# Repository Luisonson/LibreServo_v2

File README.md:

# 
An Open source controller to convert any servo motor to the best smart servo.

This project was born as a necessity of mine to build a biped robot with intelligent servos to be able to “feel the muscles” to walk more human like. In the past we had OpenServo, and I think this project inherits something from it, but OpenServo died many years ago and it didn't reach my expectations anyway (power, communications...), and the commercial alternatives are way too expensive (Dynamixel, Herkulex, Lynxmotion...).

My goal with LibreServo is to make any standard servo the “smartest” one in the market. The "gold standard" nowadays is Robotis-Dynamixel, LibreServo should be better than that, that’s my goal at least.

A few characteristics of LibreServo:

    Compatible with standard servo motors (No need to change the bottom cover of them!)
    Voltage: From 4.5V up to 18V (Recommended: 5-14V)
    Communications: RS-485 half-duplex. Max Speed 9Mbps. Daisy chained. CRC-16
    Amp: Up to 16A continuous (WSD3069DN56) (Version >2.3)
    Micro-Controller: STM32F301k8 (cortex-M4@72MHz)
    Position sensor: Magnetic encoder, 16 bits of resolution! 360 degrees (AEAT-8800). Using the servo motor potentiometer will be possible to lower the cost but will lost precision and some characteristics.
    For the encoder I have designed 3D parts to substitute the potentiometer and used the same hole/space than the original.
    LibreServo will generate their own curves (sine ramps, trapezoidal ramps, hermitian curves...)
    Current sensor: +-15A ACS711
Communication Protocol: <a href="https://www.libreservo.com/en/articulo/libreservo-commands-part-one">LibreServo Commands</a><BR>

More info in <a href="https://www.libreservo.com/en">LibreServo</a>.

<p align="center">
</p>

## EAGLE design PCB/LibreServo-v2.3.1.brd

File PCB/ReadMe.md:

Here are the files (.brd and .sch) of KiCad 7.6.0 from LibreServo.<BR>
  In the "old" folder are the previous versions of the schematics.<BR>
  In the "Gerbers" folder are the production files.
#

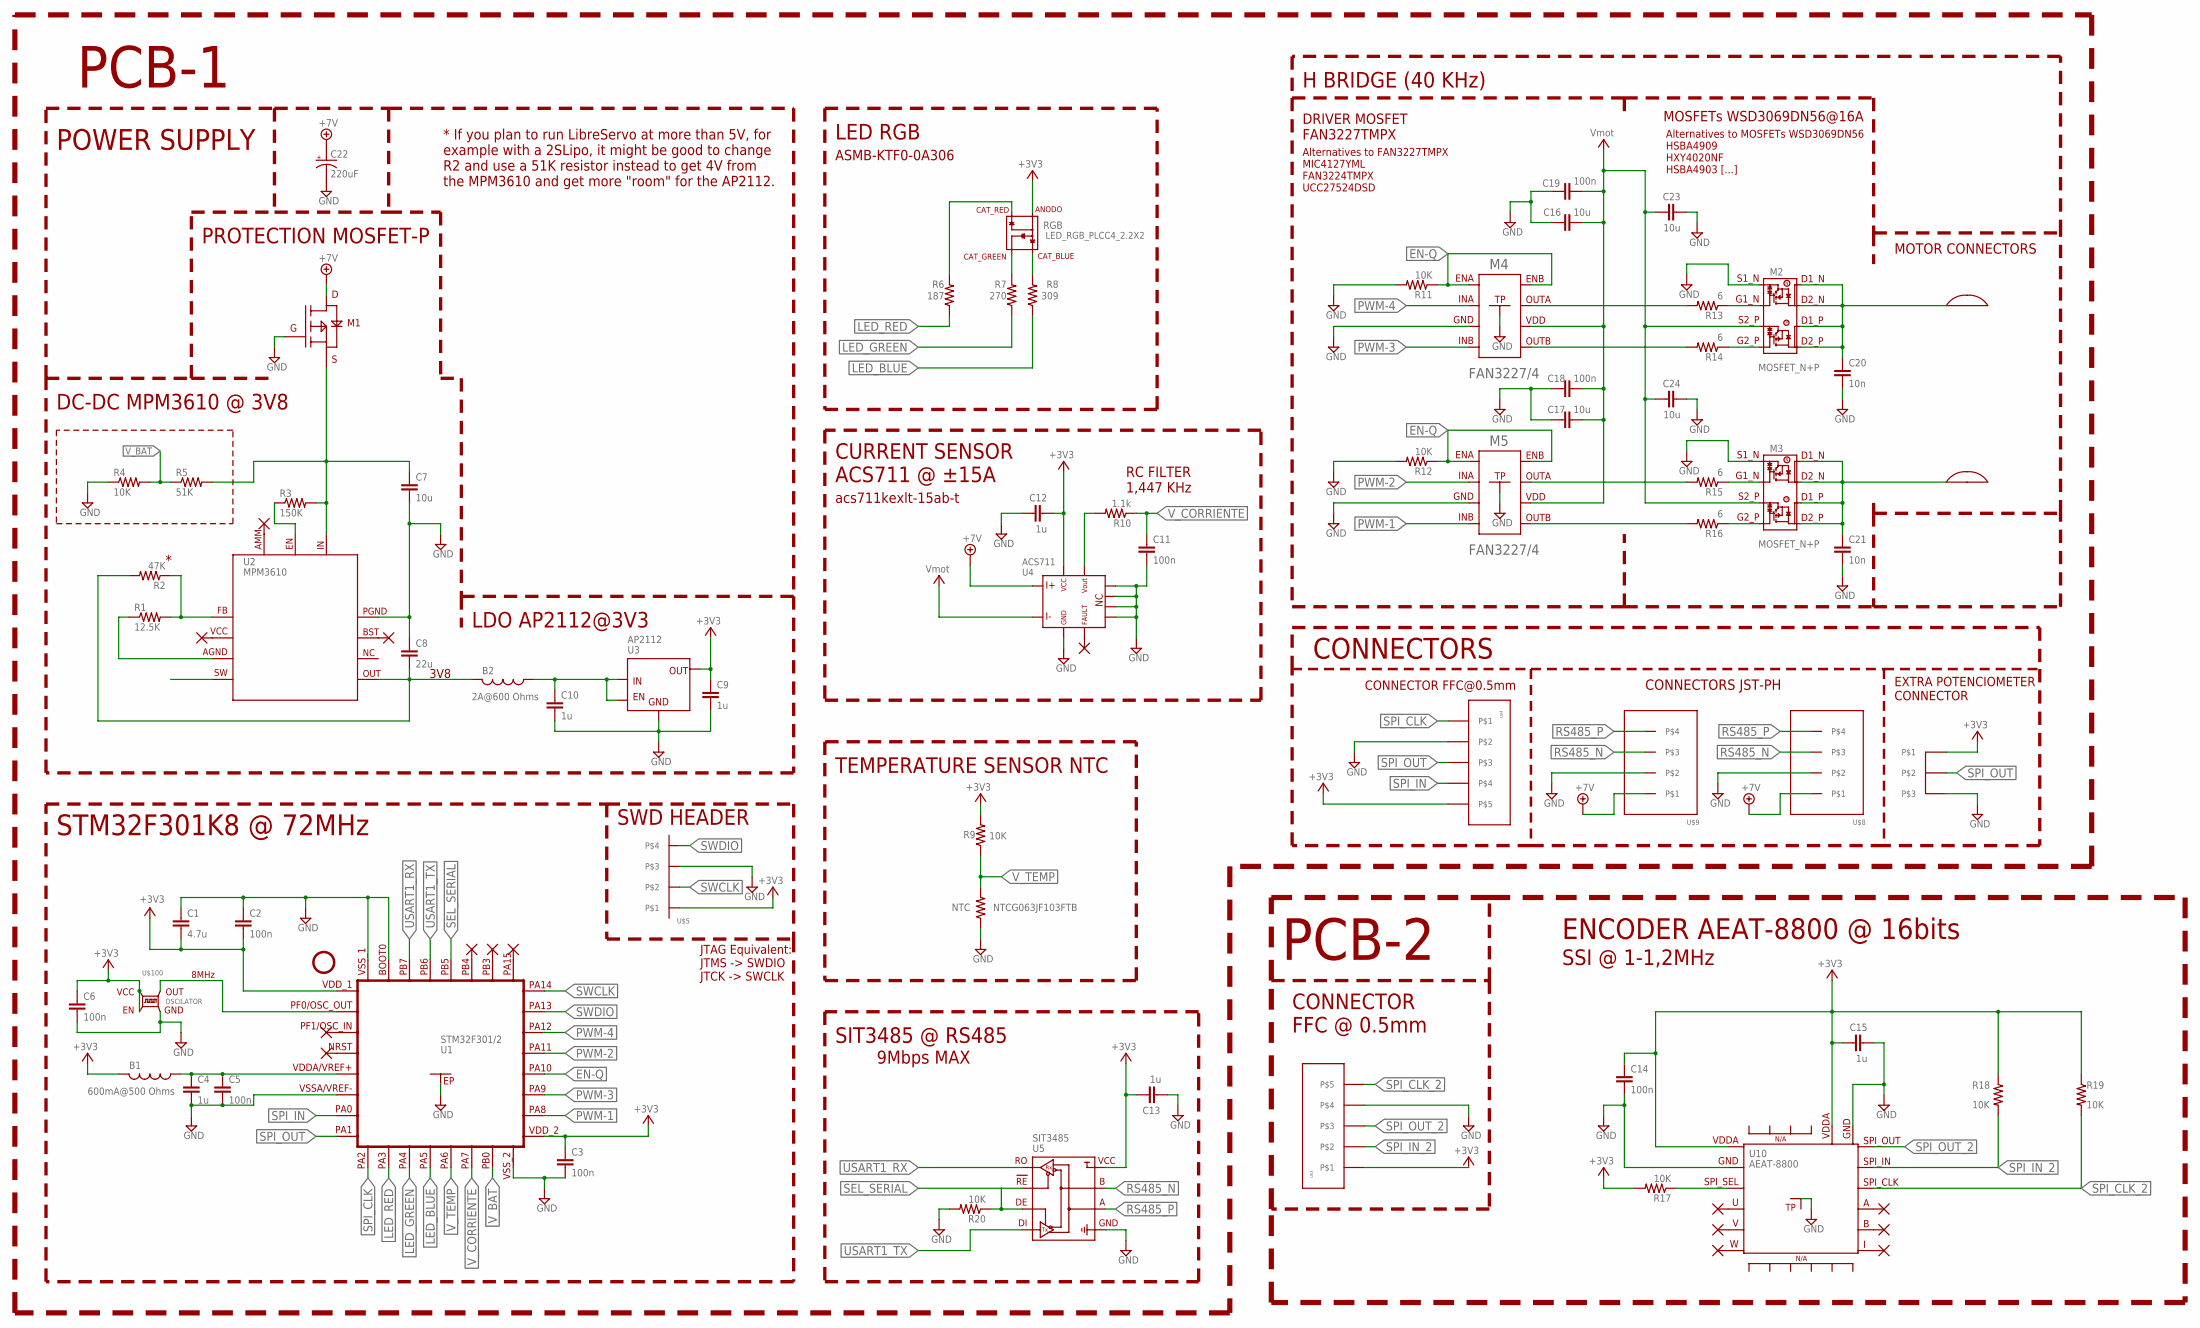
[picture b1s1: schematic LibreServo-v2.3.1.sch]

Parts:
B1: FERRITE_BEAD_0402; 0402
B2: FERRITE_BEAD_0603; 0603
C1: 4.7u; 0402
C2, C3, C5, C6, C11, C14, C18, C19: 100n; 0402
C4, C9, C10, C12, C13, C15: 1u; 0402
C7, C16, C17, C23, C24: 10u; 0603
C8: 22u; 1206
C20, C21: 10n; 0402
C22: 220uF; E2,5-6_MIN
M1: M1; SOT23
M2, M3: MOSFET_N+P; DFN5X6
M4, M5: FAN3227/4; MLP8
NTC: R-US0402_MIN; 0402_MIN
R1: 12.5K; 0402
R2: 47K; 0402
R3: 150K; 0402
R4, R9, R11, R12, R17, R18, R19, R20: 10K; 0402
R5: 51K; 0402
R6: 187; 0402
R7: 270; 0402
R8: 309; 0402
R10: 1.1k; 0402
R13, R14, R15, R16: 6; 0402
RGB: LED_RGB_PLCC4_2.2X2; PLCC-4_2.2X2
U1: STM32F301/2; QFN32
U2: MPM3610; MPM36XX
U3: AP2112; SOT25
U4: ACS711; ACS711-QFN
U5: SIT3485; MSOP-8
U10: AEAT-8800; QFN24
U$1, U$2: SLOT; SERVO_SLOT
U$3, U$4: FFC-5; FFC-5-0.5
U$5: HEADER_4_1.27_0.3
U$6: POTEN_SERVO
U$8, U$9: JST_PH-4_HOLEB; JST_PH-4_HOLE_B
U$100: OSCILATOR; OSC-2X1.6

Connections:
711_OUT: R10.2, U4.P$11
+3V3: B1.2, C1.2, C2.2, C3.1, C6.1, C9.1, C12.2, C13.2, R9.2, RGB.P$1 (ANODO), U1.1 (VDD_1), U1.17 (VDD_2), U3.5, U4.P$12, U5.P$8, U$4.P$5, U$5.P$1, U$6.P$1, U$100.P$1 (EN), U$100.P$4 (VCC)
+3V3_2: C14.1, C15.1, R17.2, R18.1, R19.1, U10.P$14, U10.P$19, U$3.P$1
+7V: C22.+, M1.P$2 (D), U4.P$1, U$8.P$1, U$9.P$1
CLK-8MHZ: U1.2 (PF0/OSC_IN), U$100.P$3 (OUT)
EN-Q: M4.P$1 (ENA), M4.P$8 (ENB), M5.P$1 (ENA), M5.P$8 (ENB), R11.1, R12.1, U1.20 (PA10)
GND: C1.1, C2.1, C3.2, C4.2, C5.2, C6.2, C7.2, C8.1, C9.2, C10.2, C11.2, C12.1, C13.1, C16.1, C17.1, C18.1, C19.1, C20.2, C21.2, C22.-, C23.2, C24.2, M1.P$1 (G), M2.P$1 (S1_N), M3.P$1 (S1_N), M4.P$3 (GND), M4.P$9 (TP), M5.P$3 (GND), M5.P$9 (TP), NTC.1, R4.1, R11.2, R12.2, R20.2, U1.6 (VSSA/VREF-), U1.16 (VSS_2), U1.31 (BOOT0), U1.32 (VSS_1), U1.EP, U2.P$12 (P$8_PGND), U2.P$13 (P$8_PGND), U2.P$14 (P$8_PGND), U3.2, U4.P$5, U4.P$7, U4.P$8, U4.P$9, U4.P$10, U5.P$5, U$4.P$2, U$5.P$3, U$6.P$3, U$8.P$2, U$9.P$2, U$100.P$2 (GND)
GND_2: C14.2, C15.2, U10.P$13, U10.P$20, U10.P$25, U$3.P$4
IN_AP2112: B2.1, C10.1, U3.1, U3.3
LED_BLUE: R8.1, U1.12 (PA5)
LED_GREEN: R7.1, U1.11 (PA4)
LED_RED: R6.1, U1.10 (PA3)
M1-OUT: C7.1, M1.P$3 (S), R3.2, R5.2, U2.P$16 (P$9_IN)
M2-OUT: C20.1, M2.P$5 (D2_P), M2.P$6 (D1_P), M2.P$7 (D2_N), M2.P$8 (D1_N), M2.P$9 (D1_N), U$1.P$1
M3-OUT: C21.1, M3.P$5 (D2_P), M3.P$6 (D1_P), M3.P$7 (D2_N), M3.P$8 (D1_N), M3.P$9 (D1_N), U$2.P$1
M4-OUTA: M4.P$7 (OUTA), R13.2
M4-OUTA-IN: M2.P$2 (G1_N), R13.1
M4-OUTB: M4.P$5 (OUTB), R14.2
M4-OUTB-IN: M2.P$4 (G2_P), R14.1
M5-OUTA: M5.P$7 (OUTA), R15.2
M5-OUTA-IN: M3.P$2 (G1_N), R15.1
M5-OUTB: M5.P$5 (OUTB), R16.2
M5-OUTB-IN: M3.P$4 (G2_P), R16.1
MPM3610_AGND: R1.1, U2.P$3 (P$3_AGND)
MPM3610_EN: R3.1, U2.P$17 (P$10_EN)
MPM3610_FB: R1.2, R2.1, U2.P$1 (P$1_FB)
MPM3610_SW: U2.P$4 (P$4_SW), U2.P$5 (P$4_SW), U2.P$6 (P$4_SW)
unnamed: R6.2, RGB.P$4 (CAT_RED)
unnamed: R7.2, RGB.P$3 (CAT_GREEN)
unnamed: R8.2, RGB.P$2 (CAT_BLUE)
unnamed: R17.1, U10.P$21
OUT_MPM3610: B2.2, C8.2, R2.2, U2.P$7 (P$5_OUT), U2.P$8 (P$5_OUT), U2.P$9 (P$5_OUT)
PWM-1: M5.P$4 (INB), U1.18 (PA8)
PWM-2: M5.P$2 (INA), U1.21 (PA11)
PWM-3: M4.P$4 (INB), U1.19 (PA9)
PWM-4: M4.P$2 (INA), U1.22 (PA12)
RS485_N: U5.P$7, U$8.P$3, U$9.P$3
RS485_P: U5.P$6, U$8.P$4, U$9.P$4
SEL_SERIAL: R20.1, U1.28 (PB5), U5.P$2, U5.P$3
SPI_CLK: U1.9 (PA2), U$4.P$1
SPI_CLK_2: R19.2, U10.P$10, U$3.P$5
SPI_IN: U1.7 (PA0), U$4.P$4
SPI_IN_2: R18.2, U10.P$11, U$3.P$2
SPI_OUT: U1.8 (PA1), U$4.P$3, U$6.P$2
SPI_OUT_2: U10.P$12, U$3.P$3
SWCLK: U1.24 (PA14), U$5.P$2
SWDIO: U1.23 (PA13), U$5.P$4
USART1_RX: U1.30 (PB7), U5.P$1
USART1_TX: U1.29 (PB6), U5.P$4
VDDA-FILTRADO: B1.1, C4.1, C5.1, U1.5 (VDDA/VREF+)
VMOT: C16.2, C17.2, C18.2, C19.2, C23.1, C24.1, M2.P$3 (S2_P), M3.P$3 (S2_P), M4.P$6 (VDD), M5.P$6 (VDD), U4.P$3
V_BAT: R4.2, R5.1, U1.15 (PB0)
V_CORRIENTE: C11.1, R10.1, U1.14 (PA7)
V_TEMP: NTC.2, R9.1, U1.13 (PA6)

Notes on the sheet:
SWD HEADER
STM32F301K8 @ 72MHz
POWER SUPPLY
PROTECTION MOSFET-P
DC-DC MPM3610 @ 3V8
LDO AP2112@3V3
LED RGB
ASMB-KTF0-0A306
CURRENT SENSOR ACS711 @ ±15A
RC FILTER 1,447 KHz
TEMPERATURE SENSOR NTC
SIT3485 @ RS485
H BRIDGE (40 KHz)
DRIVER MOSFET FAN3227TMPX
MOSFETs WSD3069DN56@16A
MOTOR CONNECTORS
PCB-2
ENCODER AEAT-8800 @ 16bits
CONNECTOR FFC @ 0.5mm
CONNECTORS
CONNECTOR FFC@0.5mm
CONNECTORS JST-PH
EXTRA POTENCIOMETER CONNECTOR
PCB-1
acs711kexlt-15ab-t
3V8
2A@600 Ohms
600mA@500 Ohms
NTCG063JF103FTB
SSI @ 1-1,2MHz
9Mbps MAX
8MHz
* If you plan to run LibreServo at more than 5V, for example with a 2SLipo, it might be good to change R2 and use a 51K resistor instead to get 4V from the MPM3610 and get more "room" for the AP2112.
Alternatives to FAN3227TMPX MIC4127YML FAN3224TMPX UCC27524DSD
Alternatives to MOSFETs WSD3069DN56 HSBA4909 HXY4020NF HSBA4903 [...]
JTAG Equivalent: JTMS -> SWDIO JTCK -> SWCLK

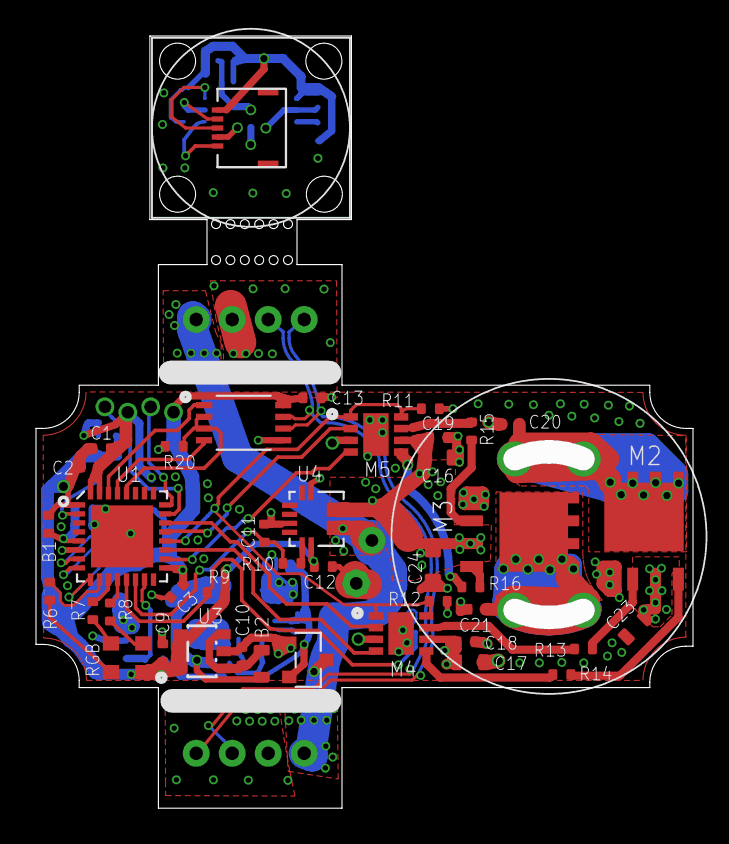
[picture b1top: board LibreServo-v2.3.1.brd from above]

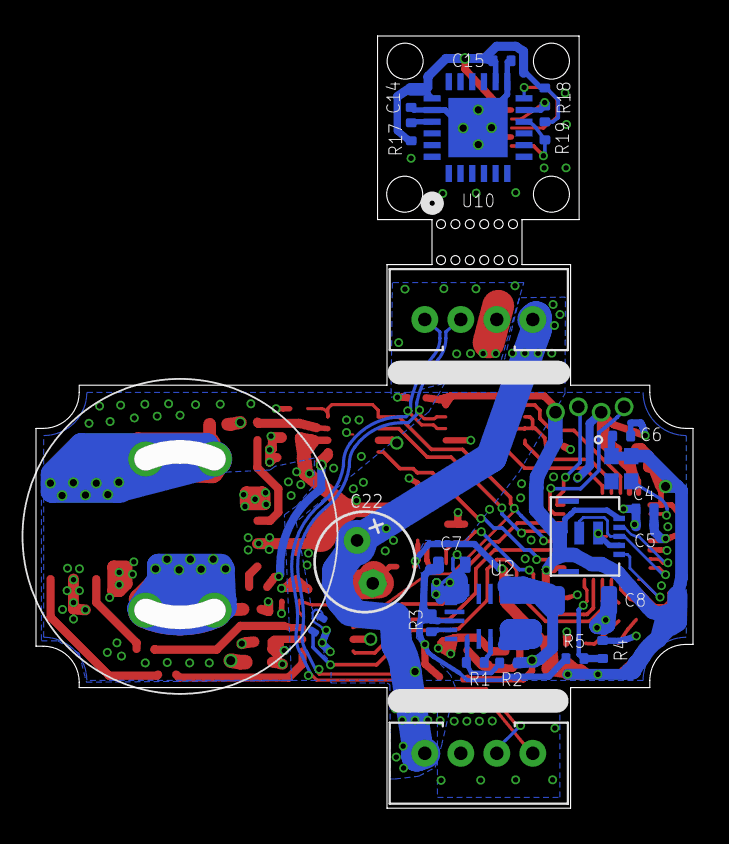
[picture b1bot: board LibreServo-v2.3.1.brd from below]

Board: 6 copper layers, 36.5 x 42.9 mm, 68 parts (23 on the bottom side), 54 nets.

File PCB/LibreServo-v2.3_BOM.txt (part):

Partlist exported from LibreServo v2.3.1 at 08/07/2024 10:16 @ https://github.com/Luisonson/LibreServo_v2 @ https://www.libreservo.com/

Part  Value               Device              Package           Description                          
B1    700mA@600Ω@100MHz   PBY100505T-601Y-N   0402              340mΩ ±25% 600Ω@100MHz 0402 Ferrite Beads 700mA                                    
B2    2A@600Ω@100MHz      VPB160808T-601Y-N   0603              100mΩ ±25% 600Ω@100MHz 0603 Ferrite Beads 2A                                     
C1    4.7u                CM05X5R475M25AH     0402              25V 4.7uF X5R ±20% 0402 Multilayer Ceramic Capacitors MLCC                                     
C2    100n                CL05B104KB54PNC     0402              50V 100nF X7R ±10% 0402 Multilayer Ceramic Capacitors MLCC                                     
C3    100n                CL05B104KB54PNC     0402              50V 100nF X7R ±10% 0402 Multilayer Ceramic Capacitors MLCC
C4    1u                  CL05A105KA5NQNC     0402              25V 1uF X5R ±10% 0402 Multilayer Ceramic Capacitors MLCC
C5    100n                CL05B104KB54PNC     0402              50V 100nF X7R ±10% 0402 Multilayer Ceramic Capacitors MLCC
C6    100n                CL05B104KB54PNC     0402              50V 100nF X7R ±10% 0402 Multilayer Ceramic Capacitors MLCC
C7    10u                 CL10A106MA8NRNC     0603              25V 10uF X5R ±20% 0603 Multilayer Ceramic Capacitors MLCC
C8    22u                 CL31A226KAHNNNE     1206              25V 22uF X5R ±10% 1206 Multilayer Ceramic Capacitors MLCC
C9    1u                  CL05A105KA5NQNC     0402              25V 1uF X5R ±10% 0402 Multilayer Ceramic Capacitors MLCC
C10   1u                  CL05A105KA5NQNC     0402              25V 1uF X5R ±10% 0402 Multilayer Ceramic Capacitors MLCC
C11   100n                CL05B104KB54PNC     0402              50V 100nF X7R ±10% 0402 Multilayer Ceramic Capacitors MLCC
C12   1u                  CL05A105KA5NQNC     0402              25V 1uF X5R ±10% 0402 Multilayer Ceramic Capacitors MLCC
C13   1u                  CL05A105KA5NQNC     0402              25V 1uF X5R ±10% 0402 Multilayer Ceramic Capacitors MLCC
C14   100n                CL05B104KB54PNC     0402              50V 100nF X7R ±10% 0402 Multilayer Ceramic Capacitors MLCC
C15   1u                  CL05A105KA5NQNC     0402              25V 1uF X5R ±10% 0402 Multilayer Ceramic Capacitors MLCC
C16   10u                 CL10A106MA8NRNC     0603              25V 10uF X5R ±20% 0603 Multilayer Ceramic Capacitors MLCC
C17   10u                 CL10A106MA8NRNC     0603              25V 10uF X5R ±20% 0603 Multilayer Ceramic Capacitors MLCC
C18   100n                CL05B104KB54PNC     0402              50V 100nF X7R ±10% 0402 Multilayer Ceramic Capacitors MLCC
C19   100n                CL05B104KB54PNC     0402              50V 100nF X7R ±10% 0402 Multilayer Ceramic Capacitors MLCC
C20   10n                 CL05B103KB5NNNC     0402              50V 10nF X7R ±10% 0402 Multilayer Ceramic Capacitors MLCC
C21   10n                 CL05B103KB5NNNC     0402              50V 10nF X7R ±10% 0402 Multilayer Ceramic Capacitors MLCC
C22   220uF               ERS1EM221E11OT      E2,5-6_MIN        220uF 25V 220mΩ@100kHz ±20% 340mA@100kHz Plugin,D6.3xL11mm Aluminum Electrolytic Capacitors - Leaded
C23   10u                 CL10A106MA8NRNC     0603              25V 10uF X5R ±20% 0603 Multilayer Ceramic Capacitors MLCC
C24   10u                 CL10A106MA8NRNC     0603              25V 10uF X5R ±20% 0603 Multilayer Ceramic Capacitors MLCC
M1    P5103EMA            P5103EMA            SOT23             P Channel 30V 3.8A 1W 85mΩ@4.5V,3.5A SOT-23(TO-236)                                     
M2    MOSFET_N+P          WSD3069DN56         DFN5X6            30V 16A 15mΩ@10V,10A 1.5V@250uA 1PCSNChannel+1PCSPChannel DFN-8(5.2x5.5)
M3    MOSFET_N+P          WSD3069DN56         DFN5X6            30V 16A 15mΩ@10V,10A 1.5V@250uA 1PCSNChannel+1PCSPChannel DFN-8(5.2x5.5)
M4    FAN3227/4           FAN3227TMPX         MLP8              Low Side 2 MOSFET 3A 12ns 9ns 4.5V~18V 3A WDFN-8(3x3) Gate Drivers
M5    FAN3227/4           FAN3227TMPX         MLP8              Low Side 2 MOSFET 3A 12ns 9ns 4.5V~18V 3A WDFN-8(3x3) Gate Drivers
NTC   10K@3380K NTC       NTCG063JF103FTB     0402_MIN          10kΩ 310uA 100mW ±1% 3380K ±1% 0201 NTC Thermistors
R1    12.5K               0402WGF1252TCE      0402              62.5mW Thick Film Resistors 50V ±100ppm/ºC ±1% 12.5kΩ 0402
R2    47K                 0402WGF4702TCE      0402              62.5mW Thick Film Resistors 50V ±100ppm/ºC ±1% 47kΩ 0402
R3    150K                0402WGF1503TCE      0402              62.5mW Thick Film Resistors 50V ±100ppm/ºC ±1% 150kΩ 0402
R4    10K                 0402WGF1002TCE      0402              62.5mW 10kΩ 50V Thick Film Resistors ±1% ±100ppm/ºC 0402
R5    51K                 TR0402B51K0Q1050Z   0402              63mW Thin Film Resistor 25V ±50ppm/ºC ±0.1% 51kΩ 0402
R6    187                 RC0402FR-07187RL    0402              62.5mW Thick Film Resistors 50V ±100ppm/ºC ±1% 187Ω 0402
R7    270                 0402WGF2700TCE      0402              62.5mW Thick Film Resistors 50V ±100ppm/ºC ±1% 270Ω 0402
R8    309                 CQ02WGF3090TCE      0402              62.5mW 50V ±100ppm/ºC ±1% 309Ω 0402
R9    10K                 0402WGF1002TCE      0402              62.5mW 10kΩ 50V Thick Film Resistors ±1% ±100ppm/ºC 0402
R10   1.1k                0402WGF1101TCE      0402              62.5mW Thick Film Resistors 50V ±100ppm/ºC ±1% 1.1kΩ 0402
R11   10K                 0402WGF1002TCE      0402              62.5mW 10kΩ 50V Thick Film Resistors ±1% ±100ppm/ºC 0402
R12   10K                 0402WGF1002TCE      0402              62.5mW 10kΩ 50V Thick Film Resistors ±1% ±100ppm/ºC 0402
R13   6                   WR04W6R04FTL        0402              62.5mW Thick Film Resistors 50V -200ppm/ºC 400ppm/ºC ±1% 6.04Ω 0402
R14   6                   WR04W6R04FTL        0402              62.5mW Thick Film Resistors 50V -200ppm/ºC 400ppm/ºC ±1% 6.04Ω 0402
R15   6                   WR04W6R04FTL        0402              62.5mW Thick Film Resistors 50V -200ppm/ºC 400ppm/ºC ±1% 6.04Ω 0402
R16   6                   WR04W6R04FTL        0402              62.5mW Thick Film Resistors 50V -200ppm/ºC 400ppm/ºC ±1% 6.04Ω 0402
R17   10K                 0402WGF1002TCE      0402              62.5mW 10kΩ 50V Thick Film Resistors ±1% ±100ppm/ºC 0402
R18   10K                 0402WGF1002TCE      0402              62.5mW 10kΩ 50V Thick Film Resistors ±1% ±100ppm/ºC 0402
R19   10K                 0402WGF1002TCE      0402              62.5mW 10kΩ 50V Thick Film Resistors ±1% ±100ppm/ºC 0402
R20   10K                 0402WGF1002TCE      0402              62.5mW 10kΩ 50V Thick Film Resistors ±1% ±100ppm/ºC 0402
RGB   LED_RGB_PLCC4_2.2X2 ASMB-KTF0-0A306     PLCC-4_2.2X2      SMD-4P,2x2.2mm Light Emitting Diodes (LED RGB)                                          
U$3   FFC-5               THD0510-05CL-GF     FFC-5-0.5         Clamshell 5P Bottom Contact Surface Mount，Right Angle 0.5mm SMD,P=0.5mm,Surface Mount，Right Angle FFC/FPC
U$4   FFC-5               THD0510-05CL-GF     FFC-5-0.5         Clamshell 5P Bottom Contact Surface Mount，Right Angle 0.5mm SMD,P=0.5mm,Surface Mount，Right Angle FFC/FPC
U$8   JST_PH-4_HOLEB      PH-4A               JST_PH-4_HOLE_B   1x4P 4P PH 1 2mm 4 Plugin,P=2mm Wire To Board Connector
U$9   JST_PH-4_HOLEB      PH-4A               JST_PH-4_HOLE_B   1x4P 4P PH 1 2mm 4 Plugin,P=2mm Wire To Board Connector
U$100 OSCILATOR@8MHz      SX1M8.000M10F30TNN  OSC-2X1.6         1.62V~3.63V ±10ppm 10mA ±30ppm CMOS 8MHz SMD2016-4P Oscillators
U1    STM32F301/2         STM32F301K8U6       QFN32             64KB 2V~3.6V ARM-M4 16KB 72MHz FLASH 24 UFQFPN-32(5x5) Microcontrollers
U2    MPM3610             MPM3610AGQV         MPM36XX           QFN-20(3x5) DC-DC Power Modules
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
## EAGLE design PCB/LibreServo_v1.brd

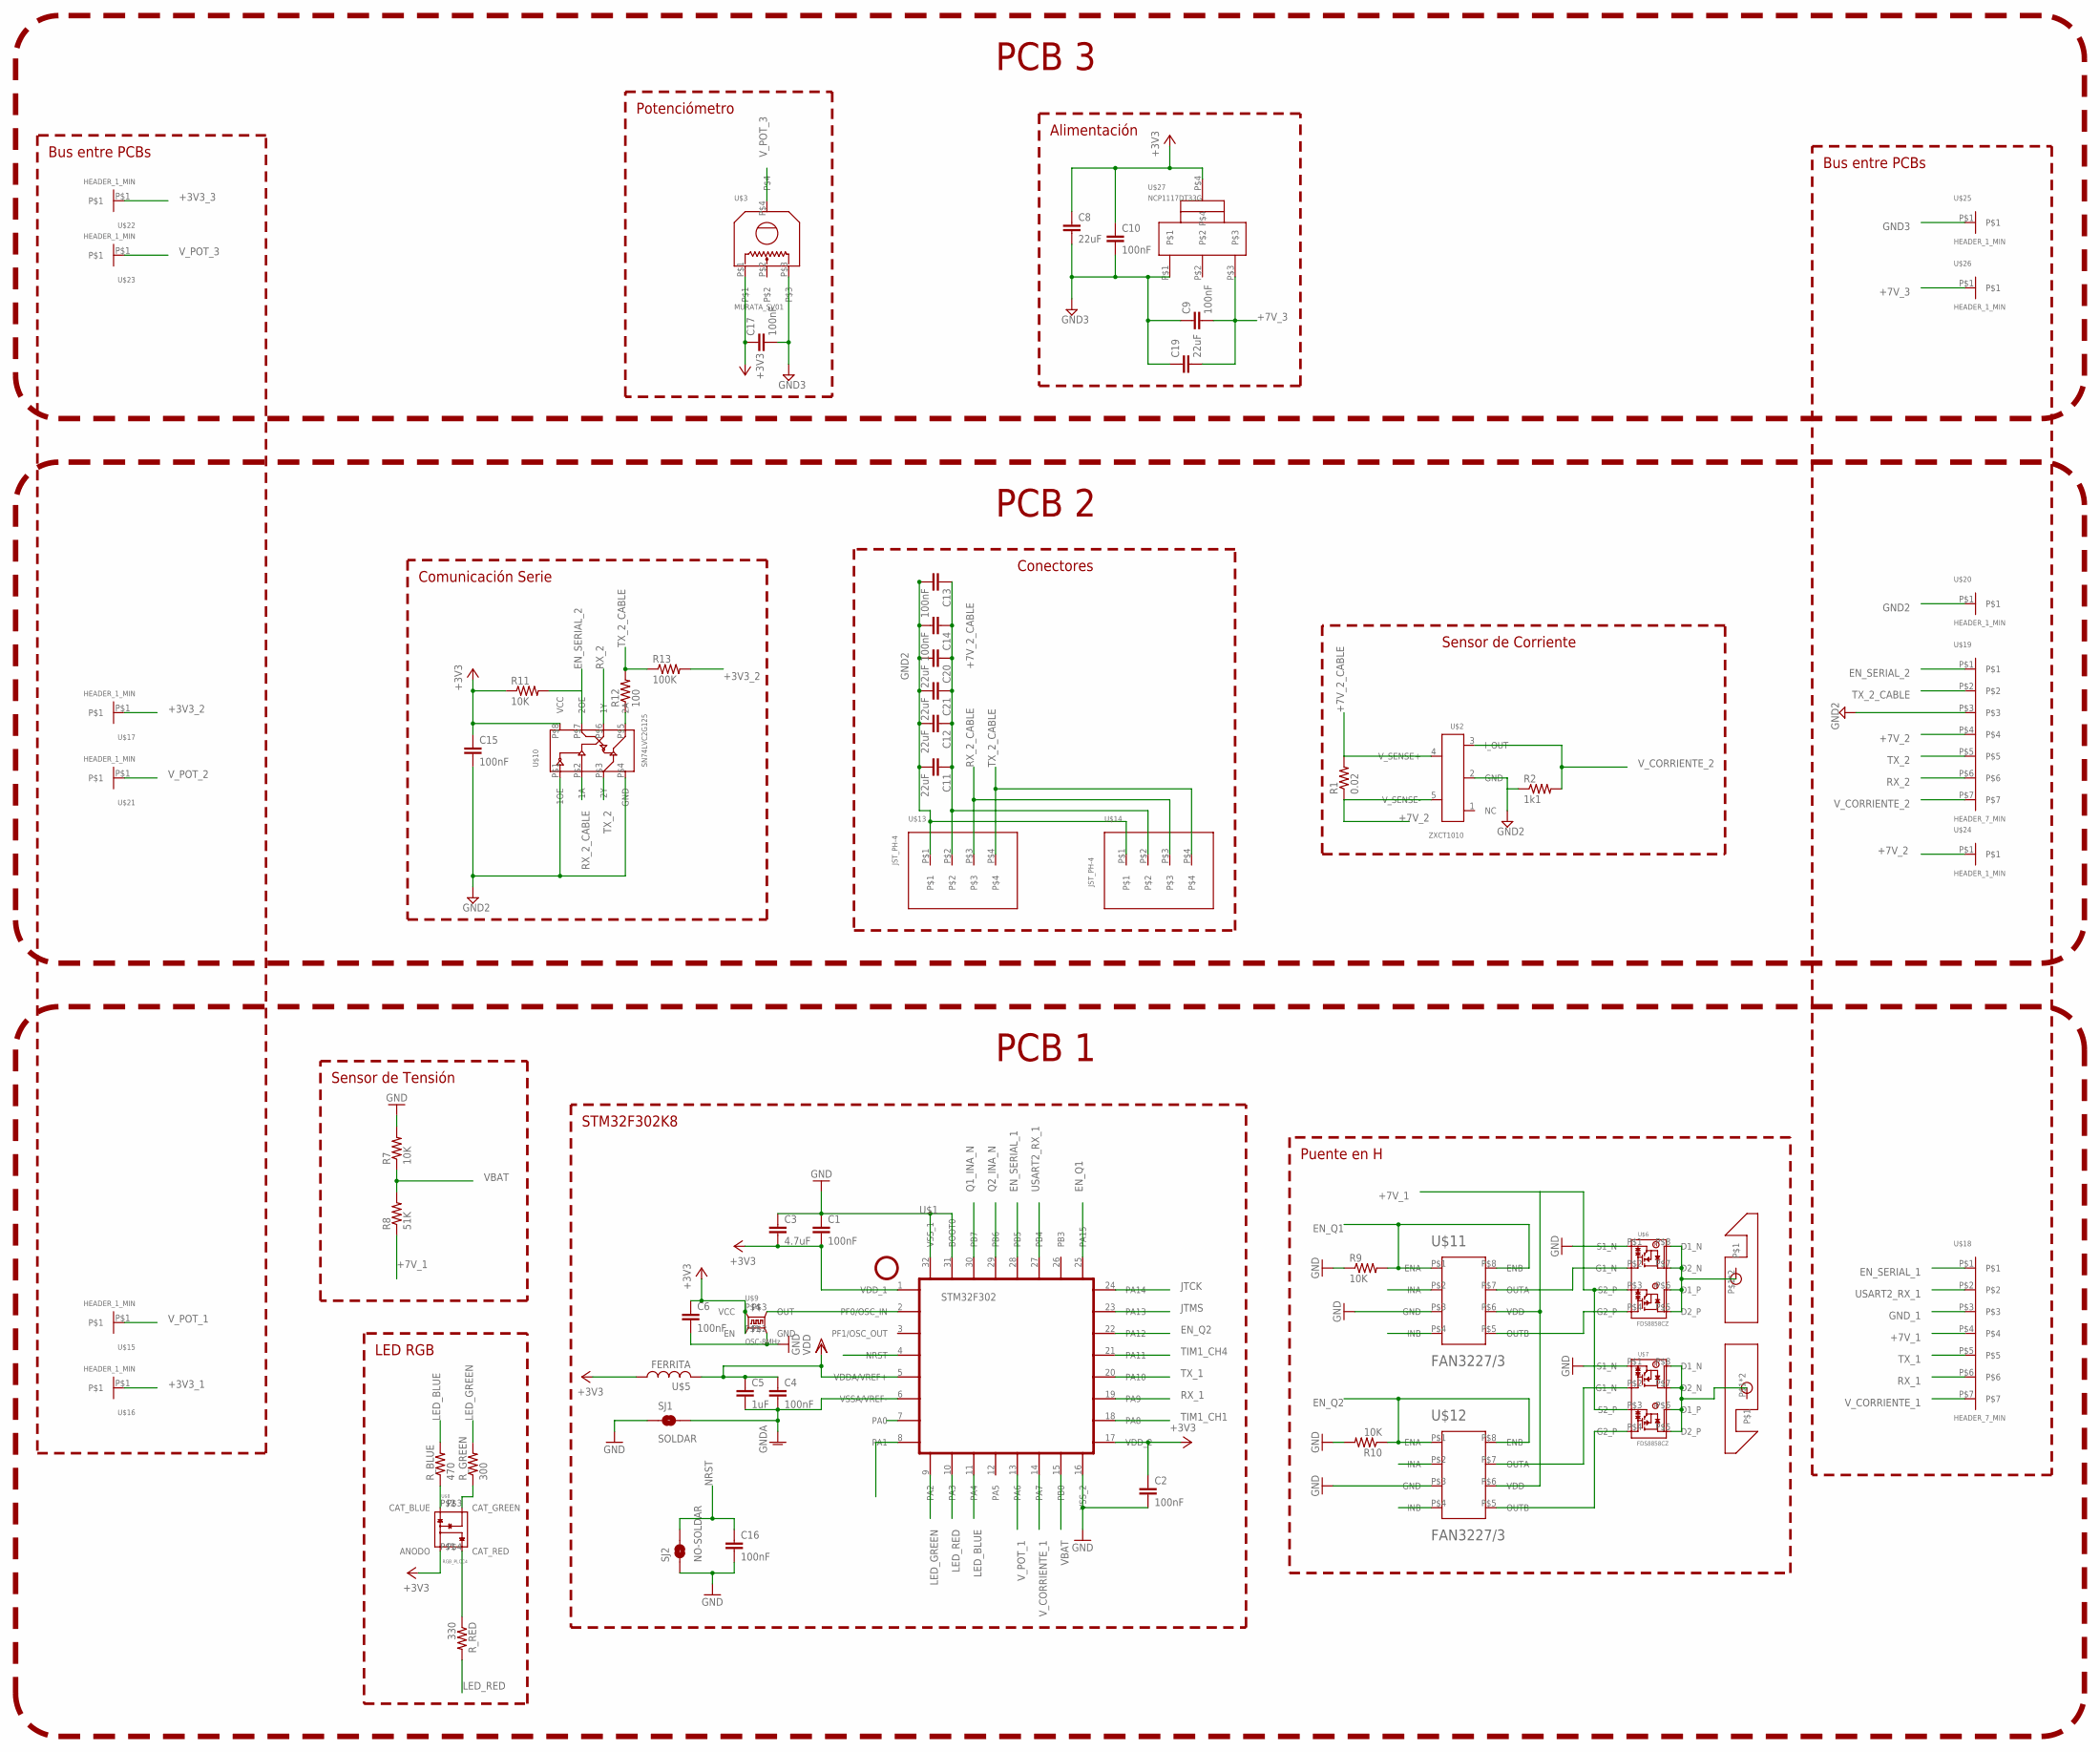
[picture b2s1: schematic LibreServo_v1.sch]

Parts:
C1, C2, C4, C6, C9, C10, C13, C14, C15, C16, C17: 100nF; C0402
C3: 4.7uF; C0402
C5: 1uF; C0402
C8, C11, C12, C19, C20, C21: 22uF; 0805_MIN
R1: 0.02; 1206_ESTRECHA
R2: 1k1; R0402
R7, R9, R10, R11: 10K; R0402
R8: 51K; R0402
R12: 100; R0402
R13: 100K; R0402
R_BLUE: 470; R0402
R_GREEN: 300; R0402
R_RED: 330; R0402
SJ1: SOLDAR; SJ_2S
SJ2: NO-SOLDAR; SJ_2S-NO
U$1: STM32F302; QFN32
U$2: ZXCT1010; SOT25
U$3: MURATA_SV01
U$4: PAD_LIBRE_SERVO_V1_A
U$5: FERRITA; 0402
U$6, U$7: FDS8858CZ; SO-8
U$8: RGB_PLCC4; PLCC4
U$9: OSC-8MHz; OSC-2.5X2
U$10: SN74LVC2G125; VSSOP-8
U$11, U$12: FAN3227/3; MLP8
U$13, U$14: JST_PH-4; JST_PH-4_HOLE
U$15, U$16, U$17, U$20, U$21, U$22, U$23, U$24, U$25, U$26: HEADER_1_MIN
U$18, U$19: HEADER_7_MIN
U$27: NCP1117DT33G; SOT223_MOD
U$28: PAD_LIBRE_SERVO_V1_B

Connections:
+3V3_1: C1.2, C2.1, C3.2, C6.1, U$1.1 (VDD_1), U$1.17 (VDD_2), U$5.1, U$8.P$1 (ANODO), U$9.P$1 (EN), U$9.P$4 (VCC), U$16.P$1
+3V3_2: C15.1, R11.1, R13.2, U$10.P$8 (VCC), U$17.P$1
+3V3_3: C8.1, C10.1, C17.1, U$3.P$1, U$22.P$1, U$27.P$4
+7V_1: R8.1, U$6.P$3 (S2_P), U$7.P$3 (S2_P), U$11.P$6 (VDD), U$12.P$6 (VDD), U$18.P$4
+7V_2: R1.1, U$2.5 (V_SENSE-), U$19.P$4, U$24.P$1
+7V_2_CABLE: C11.1, C12.1, C13.1, C14.1, C20.1, C21.1, R1.2, U$2.4 (V_SENSE+), U$13.P$2, U$14.P$2
+7V_3: C9.2, C19.2, U$26.P$1, U$27.P$3
EN_Q1: R9.2, U$1.25 (PA15), U$11.P$1 (ENA), U$11.P$8 (ENB)
EN_Q2: R10.1, U$1.22 (PA12), U$12.P$1 (ENA), U$12.P$8 (ENB)
EN_SERIAL_1: U$1.28 (PB5), U$18.P$1
EN_SERIAL_2: R11.2, U$10.P$7 (2OE), U$19.P$1
GND2: C11.2, C12.2, C13.2, C14.2, C15.2, C20.2, C21.2, R2.1, U$2.2 (GND), U$10.P$1 (1OE), U$10.P$4 (GND), U$13.P$1, U$14.P$1, U$19.P$3, U$20.P$1
GND3: C8.2, C9.1, C10.2, C17.2, C19.1, U$3.P$3, U$25.P$1, U$27.P$1
GNDA: C4.2, C5.2, SJ1.2, U$1.6 (VSSA/VREF-)
GND_1: C1.1, C2.2, C3.1, C6.2, C16.2, R7.2, R9.1, R10.2, SJ1.1, SJ2.1, U$1.16 (VSS_2), U$1.31 (BOOT0), U$1.32 (VSS_1), U$6.P$1 (S1_N), U$7.P$1 (S1_N), U$9.P$2 (GND), U$11.P$3 (GND), U$12.P$3 (GND), U$18.P$3
JTCK: U$1.24 (PA14)
JTMS: U$1.23 (PA13)
LED_BLUE: R_BLUE.2, U$1.11 (PA4)
LED_GREEN: R_GREEN.2, U$1.9 (PA2)
LED_RED: R_RED.2, U$1.10 (PA3)
unnamed: R_BLUE.1, U$8.P$2 (CAT_BLUE)
unnamed: R_GREEN.1, U$8.P$3 (CAT_GREEN)
unnamed: R_RED.1, U$8.P$4 (CAT_RED)
unnamed: U$1.2 (PF0/OSC_IN), U$9.P$3 (OUT)
unnamed: R12.1, U$10.P$5 (2A)
unnamed: U$6.P$2 (G1_N), U$11.P$7 (OUTA)
unnamed: U$6.P$4 (G2_P), U$11.P$5 (OUTB)
unnamed: U$7.P$2 (G1_N), U$12.P$7 (OUTA)
unnamed: U$7.P$4 (G2_P), U$12.P$5 (OUTB)
unnamed: U$6.P$5 (D2_P), U$6.P$6 (D1_P), U$6.P$7 (D2_N), U$6.P$8 (D1_N), U$28.P$1, U$28.P$2
unnamed: U$4.P$1, U$4.P$2, U$7.P$5 (D2_P), U$7.P$6 (D1_P), U$7.P$7 (D2_N), U$7.P$8 (D1_N)
NRST: C16.1, SJ2.2, U$1.4 (NRST)
Q1_INA_N: U$1.30 (PB7), U$11.P$2 (INA)
Q2_INA_N: U$1.29 (PB6), U$12.P$2 (INA)
RX_1: U$1.19 (PA9), U$18.P$6
RX_2: U$10.P$6 (1Y), U$19.P$6
RX_2_CABLE: U$10.P$2 (1A), U$13.P$3, U$14.P$3
TIM1_CH1: U$1.18 (PA8), U$12.P$4 (INB)
TIM1_CH4: U$1.21 (PA11), U$11.P$4 (INB)
TX_1: U$1.20 (PA10), U$18.P$5
TX_2: U$10.P$3 (2Y), U$19.P$5
TX_2_CABLE: R12.2, R13.1, U$13.P$4, U$14.P$4, U$19.P$2
USART2_RX_1: U$1.27 (PB4), U$18.P$2
VBAT: R7.1, R8.2, U$1.15 (PB0)
VDD: C4.1, C5.1, U$1.5 (VDDA/VREF+), U$5.2
V_CORRIENTE_1: U$1.14 (PA7), U$18.P$7
V_CORRIENTE_2: R2.2, U$2.3 (I_OUT), U$19.P$7
V_POT_1: U$1.13 (PA6), U$15.P$1
V_POT_2: U$21.P$1
V_POT_3: U$3.P$4, U$23.P$1

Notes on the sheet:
Potenciómetro
Conectores
Sensor de Corriente
Comunicación Serie
Alimentación
LED RGB
Sensor de Tensión
Puente en H
STM32F302K8
Bus entre PCBs
PCB 1
PCB 2
PCB 3

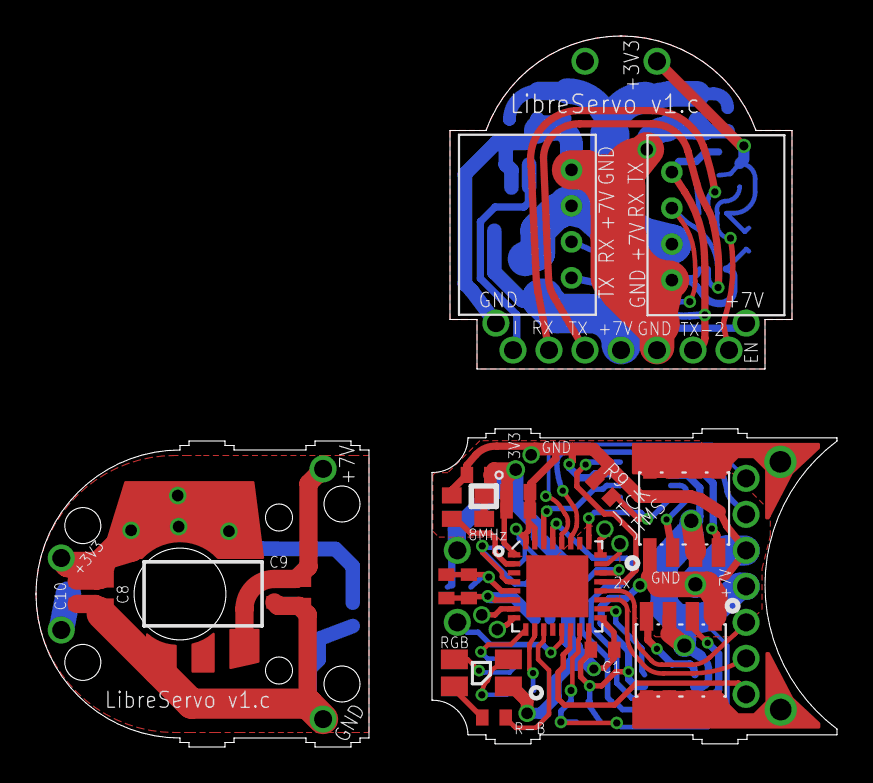
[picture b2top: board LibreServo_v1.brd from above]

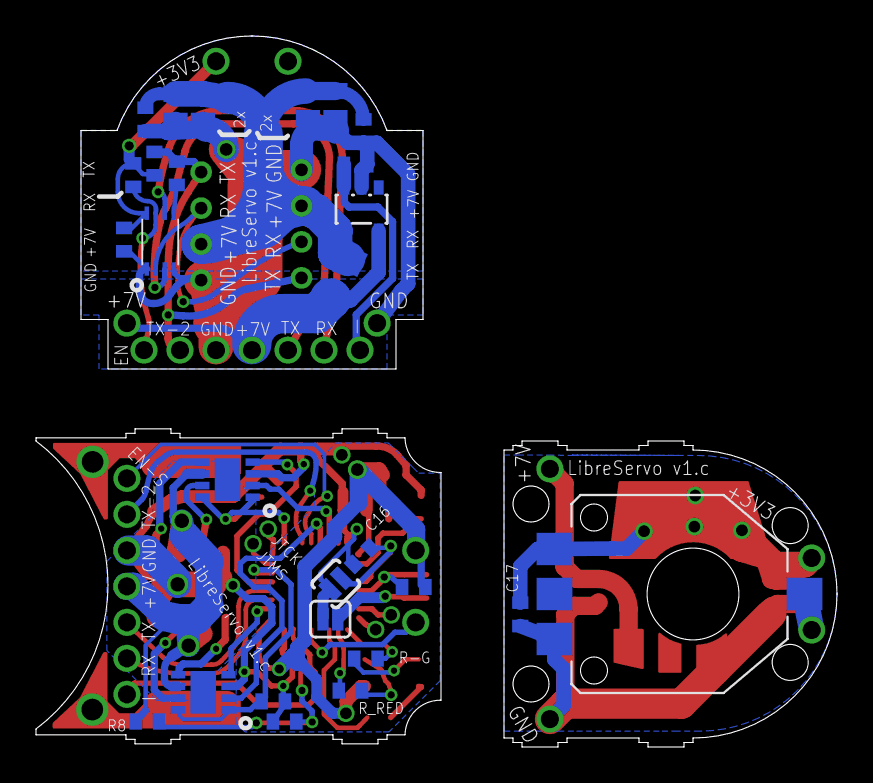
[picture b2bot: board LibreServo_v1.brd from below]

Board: 2 copper layers, 44.5 x 39.5 mm, 61 parts (27 on the bottom side), 47 nets.

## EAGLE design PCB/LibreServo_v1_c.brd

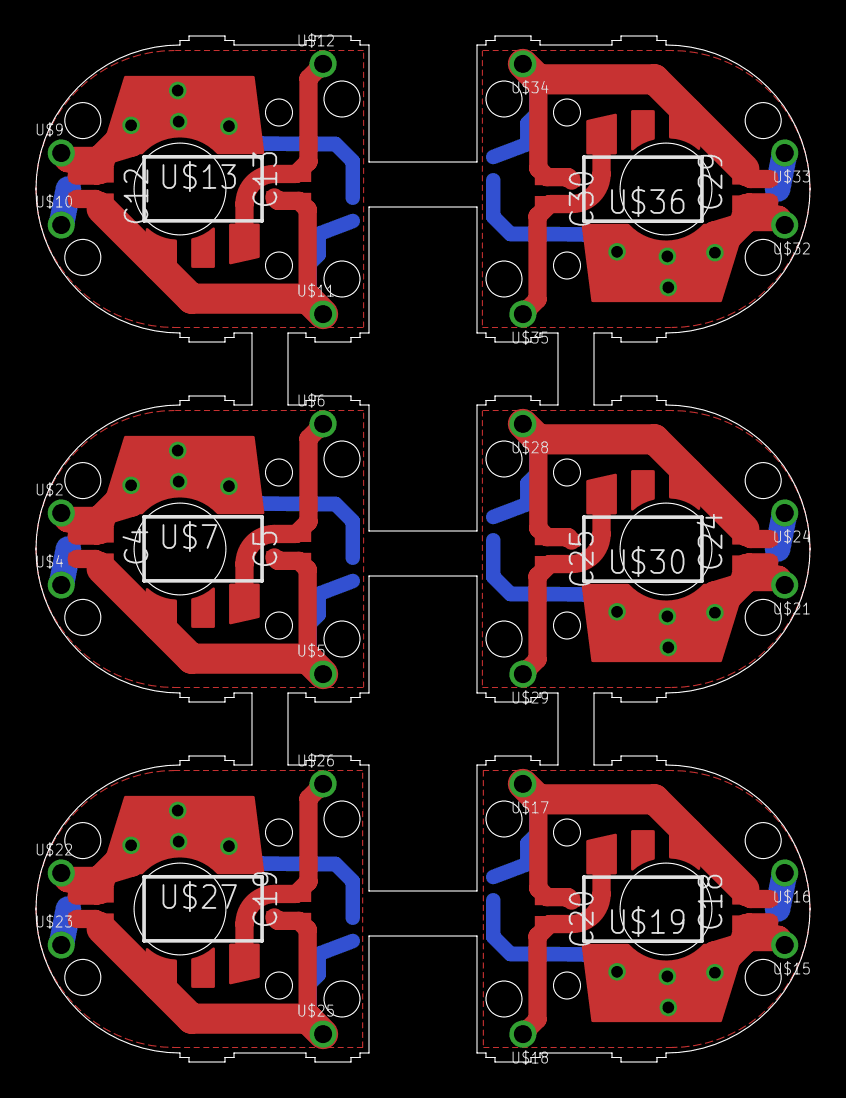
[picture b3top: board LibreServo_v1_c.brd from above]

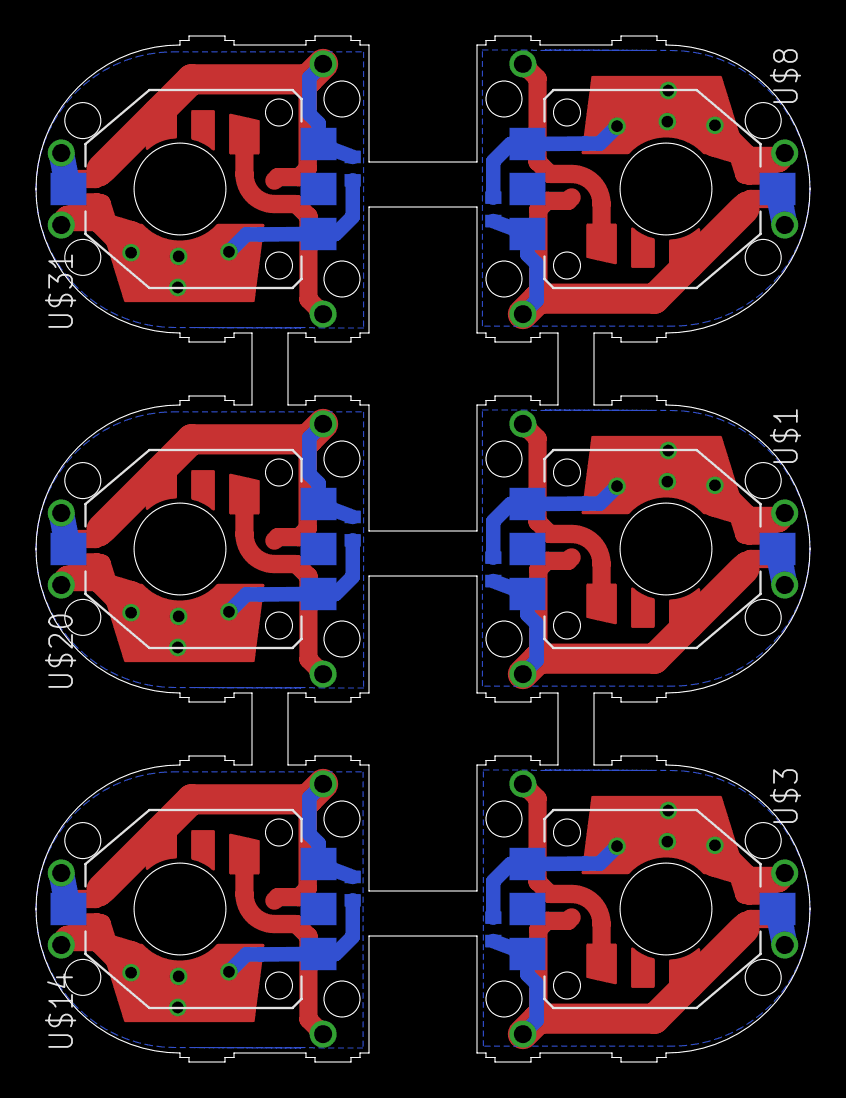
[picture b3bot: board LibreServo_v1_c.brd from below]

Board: 2 copper layers, 43.0 x 57.0 mm, 66 parts (12 on the bottom side), 24 nets.

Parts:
C1, C2, C3, C6, C7, C9, C10, C11, C14, C15, C16, C17, C21, C22, C23, C26, C27, C28: 100nF; C0402
C4, C5, C8, C12, C13, C18, C19, C20, C24, C25, C29, C30: 22uF; 0805_MIN
U$1, U$3, U$8, U$14, U$20, U$31: MURATA_SV01
U$2, U$4, U$5, U$6, U$9, U$10, U$11, U$12, U$15, U$16, U$17, U$18, U$21, U$22, U$23, U$24, U$25, U$26, U$28, U$29, U$32, U$33, U$34, U$35: HEADER_1_MIN
U$7, U$13, U$19, U$27, U$30, U$36: NCP1117DT33G; SOT223_MOD

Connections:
+3V3_1: C1.1, C3.1, C4.1, U$1.P$1, U$2.P$1, U$7.P$4
+3V3_2: C6.1, C11.1, C12.1, U$8.P$1, U$9.P$1, U$13.P$4
+3V3_3: C8.1, C10.1, C17.1, U$3.P$1, U$22.P$1, U$27.P$4
+3V3_4: C14.1, C16.1, C18.1, U$14.P$1, U$15.P$1, U$19.P$4
+3V3_5: C21.1, C23.1, C24.1, U$20.P$1, U$21.P$1, U$30.P$4
+3V3_6: C26.1, C28.1, C29.1, U$31.P$1, U$32.P$1, U$36.P$4
+7V_1: C2.2, C5.2, U$6.P$1, U$7.P$3
+7V_2: C7.2, C13.2, U$12.P$1, U$13.P$3
+7V_3: C9.2, C19.2, U$26.P$1, U$27.P$3
+7V_4: C15.2, C20.2, U$18.P$1, U$19.P$3
+7V_5: C22.2, C25.2, U$29.P$1, U$30.P$3
+7V_6: C27.2, C30.2, U$35.P$1, U$36.P$3
GND1: C1.2, C2.1, C3.2, C4.2, C5.1, U$1.P$3, U$5.P$1, U$7.P$1
GND2: C6.2, C7.1, C11.2, C12.2, C13.1, U$8.P$3, U$11.P$1, U$13.P$1
GND3: C8.2, C9.1, C10.2, C17.2, C19.1, U$3.P$3, U$25.P$1, U$27.P$1
GND4: C14.2, C15.1, C16.2, C18.2, C20.1, U$14.P$3, U$17.P$1, U$19.P$1
GND5: C21.2, C22.1, C23.2, C24.2, C25.1, U$20.P$3, U$28.P$1, U$30.P$1
GND6: C26.2, C27.1, C28.2, C29.2, C30.1, U$31.P$3, U$34.P$1, U$36.P$1
V_POT_1: U$1.P$4, U$4.P$1
V_POT_2: U$8.P$4, U$10.P$1
V_POT_3: U$3.P$4, U$23.P$1
V_POT_4: U$14.P$4, U$16.P$1
V_POT_5: U$20.P$4, U$24.P$1
V_POT_6: U$31.P$4, U$33.P$1

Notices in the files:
Src/main.c:
LibreServo by Luis Picó is licensed under a Creative Commons
Attribution-ShareAlike 4.0 International License
README.md:
cc-by-sa
parts and their libraries:
SparkFun-Passives: Licensing: CC v3.0 Share-Alike You are welcome to use this library for commercial purposes.
